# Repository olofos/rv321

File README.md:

# rv321

rv321 is an RISC-V processor implemented using 74HC series logic. Currently the RV32E base instruction set is supported. The design has been simulated using [hneemann's Digital](https://github.com/hneemann/Digital). The simulated circuit also supports the C and Zicsr extensions, though these are not fully implemented in the hardware. The circuit is highly modular, and support for these extra extensions, or for the full RV32I base instruction set, can easily be added by changing only some of the modules.

The rv321 is implemented with a [bit-serial architecture](https://en.wikipedia.org/wiki/Bit-serial_architecture) where, for example, the ALU acts on one bit at a time. This makes the CPU very slow, each instruction requires around 100 clock cycles. The benefit of this architecture is that a one bit ALU is much smaller than a 32-bit ALU and that internal data paths only require a single line instead of a big parallel bus. This makes it possible to implement various modules as individual components connected through simple cables.

## Supported Instructions

The CPU supports all the instructions of the RV32E as well as the C and Zicsr extensions. However, the instructions are not completely decoded, which means that some illegal instructions will be incorrectly interpreted as valid instructions. This mostly affect instruction encodings that are not defined in the RISC-V specification. However, a few encodings that are valid RISC-V instructions, such as `sret` and `uret` will be erroneously decoded instead of raising an illegal instruction exception, even though these instructions are illegal since code on rv321 only runs in machine mode.

## CSRs

Currently the following CSRs are implemented:

* `mstatus`
* `mepc`
* `mtvec`
* `mscratch`
* `mcause`
* `mip`
* `mie`

All other CSRs are read as zero. Note that reading from or writing to an invalid CSR does *not* cause an illegal instruction exception.

## Traps and Interrupts

# Technical Details

The rv321 CPU is microcoded with the code stored in four 128kB parallel flash ROMs. The instructions are decoded by addressing these ROMs by 10 bits of the opcode, together with a six bit step counter and a flag bit, which is used by for example the branch instructions. Each opcode is processed in a number of *steps*, which in turn consist of either one or four *clock cycles*. There are two types of clock cycles: *control cycles* and *bus cycles*. During a control cycle only the control lines are being changed, while bus cycles are used to transfer data along the various internal and external buses. A step with a control cycle is always a single cycle long, but a step with bus cycles can be either one or four cycles long. 

Internal registers are implemented using shift registers that feed back into themselves, effectively creating delay line memories. Because of this, the bus cycles always have to come in groups of 32. Most data transfers are 32 bits and thus automatically take 32 bus cycles to complete anyway. However, there are a couple of cases where a shorter data transfer has to be extended by extra bus cycles to keep the registers in sync. One such examples is storing a single byte to memory, where only 8 cycles are needed for the actual data transfer, but an additional 24 cycles are needed to keep the alignment of the registers (note that a load of an 8 bit byte would always need 32 bus cycles since we need to fill the upper 24 bit with either zeros or the sign extension of the loaded byte). A second example is when transferring a 12 bit CSR address, where a padding of 20 cycles is necessary. These extra dummy bus cycles could have been avoided by gating the bus clock to registers that are not involved in the transfer, but the current design saves a bit of complexity by not introducing extra clock gates and control lines to drive them. 

## The ALU

The ALU supports the following operations:

* Bitwise boolean operations: `and`, `or` and `xor`
* Addition and subtraction
* Comparisons: equality, signed less-than and unsigned less-than
* Logical shift left, logical shift right and arithmetic shift right

The first three sets of operations are fairly straight forward.

The shift operations are more interesting. It does not use a full 32 bit barrel shifter since this would take up quite a bit of space. Instead the HEF4557B variable length shift register is used as intermediate storage during the computation (the same type of shift register is used in several other places in the rv321 as a convenient serial-in serial-out shift register with a fairly large number of bits, but the shifter in the ALU is the only circuitry that takes advantage of the possibility to vary the length of the shift register). The computation of a value shifted left or right by `n` bits goes in several steps:

1. Use the addition circuitry of the ALU to calculate the needed shift register length: `L = 32 + n` for a left shift and `L = 32 - n` for a right shift
1. Configure the HEF4557B shift register to be `L` bits long and clear its content
1. Shift in 32 bits of input data into the shift register
1. Shift out 32 bits of output data from the shift register

If the shift register length `L` is less than 32 (as is the case for a right shift with `n > 0`) we fill the remaining bits with either zero for a logical shift, or with the top bit of the output (the sign bit) for an arithmetic shift. The sign bit is stored in an extra flip flop which is set in the previous step.

As an example let us shift `0x87654321` by 12 bits to the left

1. The length of the shift register is `L = 32 + 12 = 44`.
1. The shift register is cleared. Its content is `0x00000000000`.
1. We shift in our 32 bits of data, starting with the least significant bit. After this the content of the shift register is `0x87654321000`.
1. We shift out 32 bits of output data, starting with the least significant bit. The result is the bottom four bytes of the shift register, `0x54321000`, which is exactly the expected result. The shift register still contains `0x00000000876`, but these bits are never used.

As a second example let us take the arithmetical shift `0x87654321` by 12 bits to the right

1. The length of the shift register is `L = 32 - 12 = 20`.
1. The shift register is cleared. Its content is `0x00000`.
1. We shift in our 32 bits of data, starting with the least significant bit. After this the content of the shift register is `0x87654`. Note that the lowest 12 bits have been discarded since they did not fit in the register.
1. We shift out 32 bits of output data, starting with the least significant bit. Since the shift register now contains less than 32 bits, we repeatedly shift in the sign bit of the input, which is our case is one. The resulting output is `0xFFF87654`, which again is the expected result. The shift register is left containing `0xFFFFF`.

## Possible Optimisations

The bit-serial architecture makes the rv321 CPU very inefficient. However, there is room for optimisation of the current implementation. There are two main steps for each instruction. First the instruction is fetched and then it is executed. The fetching is exactly the same for all instructions. It would be more efficient to begin fetching the next instruction while executing the previous instruction. This would make any instruction that does not affect the program counter or access memory run faster. However, this would require a more complicated reset circuit, to ensure that the very first instruction is properly fetched, and some parts of the circuit are made simpler by the fact that each instruction has a well-defined start and end. Moreover, the program counter is currently always routed through the ALU, so that there is only one source of memory addresses. For the ALU to run simultaneously with the loading of the memory address from the program counter, a new multiplexer would need to be added.

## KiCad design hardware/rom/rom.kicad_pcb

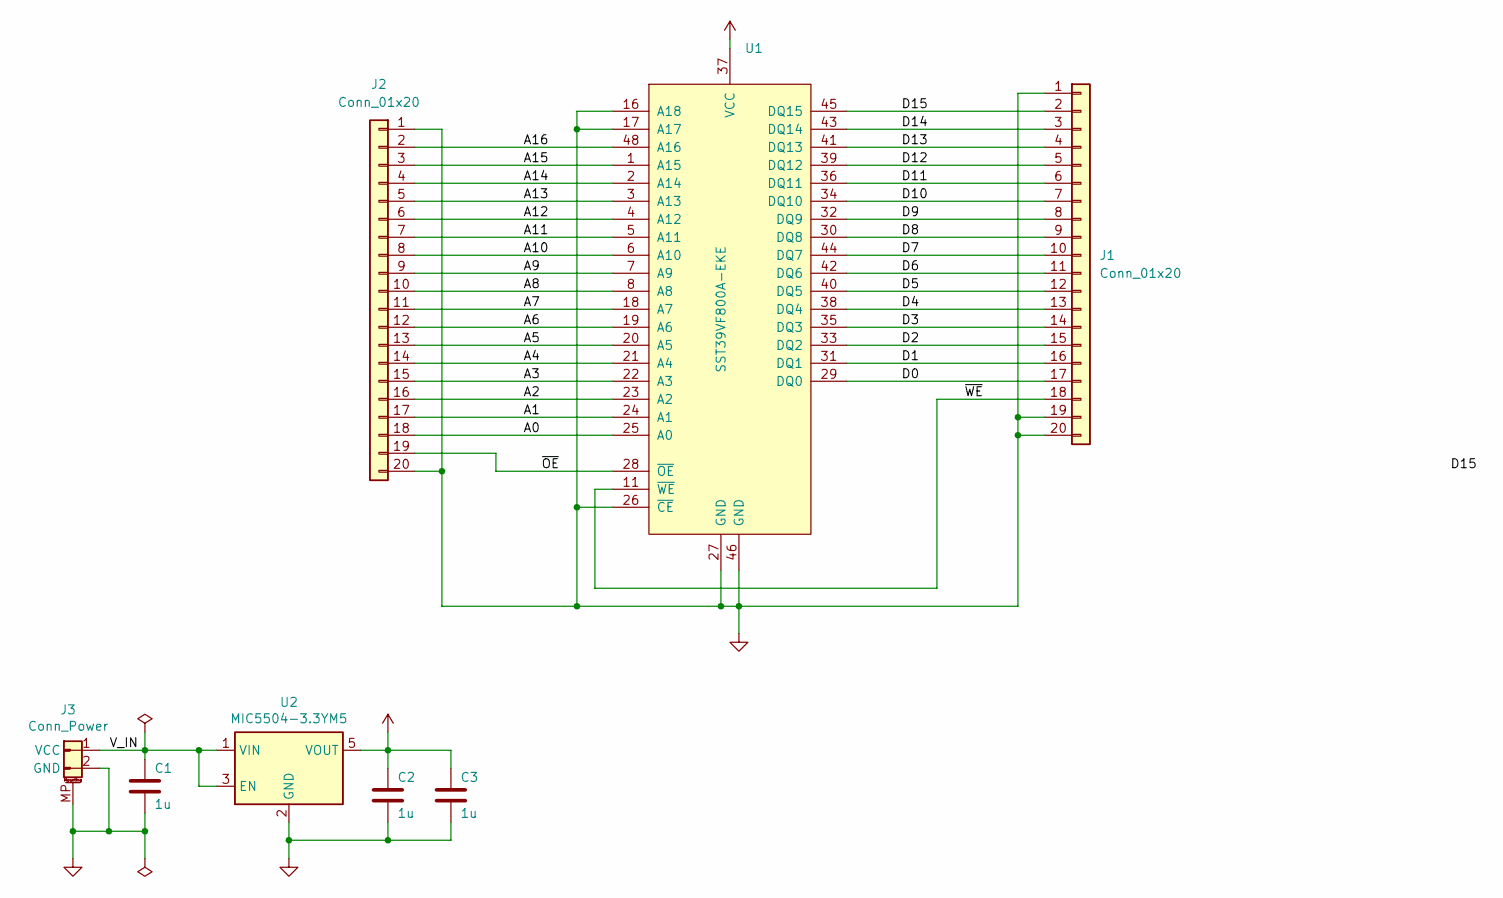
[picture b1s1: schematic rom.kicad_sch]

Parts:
C1, C2, C3: 1u; C_0805_2012Metric_Pad1.18x1.45mm_HandSolder
J1, J2: Conn_01x20; IDC-Header_2x10_P2.54mm_Vertical
J3: Conn_Power; JST_PH_S2B-PH-SM4-TB_1x02-1MP_P2.00mm_Horizontal
U1: SST39VF800A-EKE; TSOP-I-48_18.4x12mm_P0.5mm
U2: MIC5504-3.3YM5; SOT-23-5_HandSoldering

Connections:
/A0: J2.18, U1.25 (A0)
/A1: J2.17, U1.24 (A1)
/A2: J2.16, U1.23 (A2)
/A3: J2.15, U1.22 (A3)
/A4: J2.14, U1.21 (A4)
/A5: J2.13, U1.20 (A5)
/A6: J2.12, U1.19 (A6)
/A7: J2.11, U1.18 (A7)
/A8: J2.10, U1.8 (A8)
/A9: J2.9, U1.7 (A9)
/A10: J2.8, U1.6 (A10)
/A11: J2.7, U1.5 (A11)
/A12: J2.6, U1.4 (A12)
/A13: J2.5, U1.3 (A13)
/A14: J2.4, U1.2 (A14)
/A15: J2.3, U1.1 (A15)
/A16: J2.2, U1.48 (A16)
/D0: J1.17, U1.29 (DQ0)
/D1: J1.16, U1.31 (DQ1)
/D2: J1.15, U1.33 (DQ2)
/D3: J1.14, U1.35 (DQ3)
/D4: J1.13, U1.38 (DQ4)
/D5: J1.12, U1.40 (DQ5)
/D6: J1.11, U1.42 (DQ6)
/D7: J1.10, U1.44 (DQ7)
/D8: J1.9, U1.30 (DQ8)
/D9: J1.8, U1.32 (DQ9)
/D10: J1.7, U1.34 (DQ10)
/D11: J1.6, U1.36 (DQ11)
/D12: J1.5, U1.39 (DQ12)
/D13: J1.4, U1.41 (DQ13)
/D14: J1.3, U1.43 (DQ14)
/D15: J1.2, U1.45 (DQ15)
/V_IN: C1.2, J3.1 (VCC), U2.1 (VIN), U2.3 (EN)
/~OE: J2.19, U1.28 (~OE)
/~WE: J1.18, U1.11 (~WE)
GND: C1.1, C2.1, C3.1, J1.1, J1.19, J1.20, J2.1, J2.20, J3.2 (GND), J3.MP, U1.16 (A18), U1.17 (A17), U1.26 (~CE), U1.27 (GND), U1.46 (GND), U2.2 (GND)
VCC: C2.2, C3.2, U1.37 (VCC), U2.5 (VOUT)

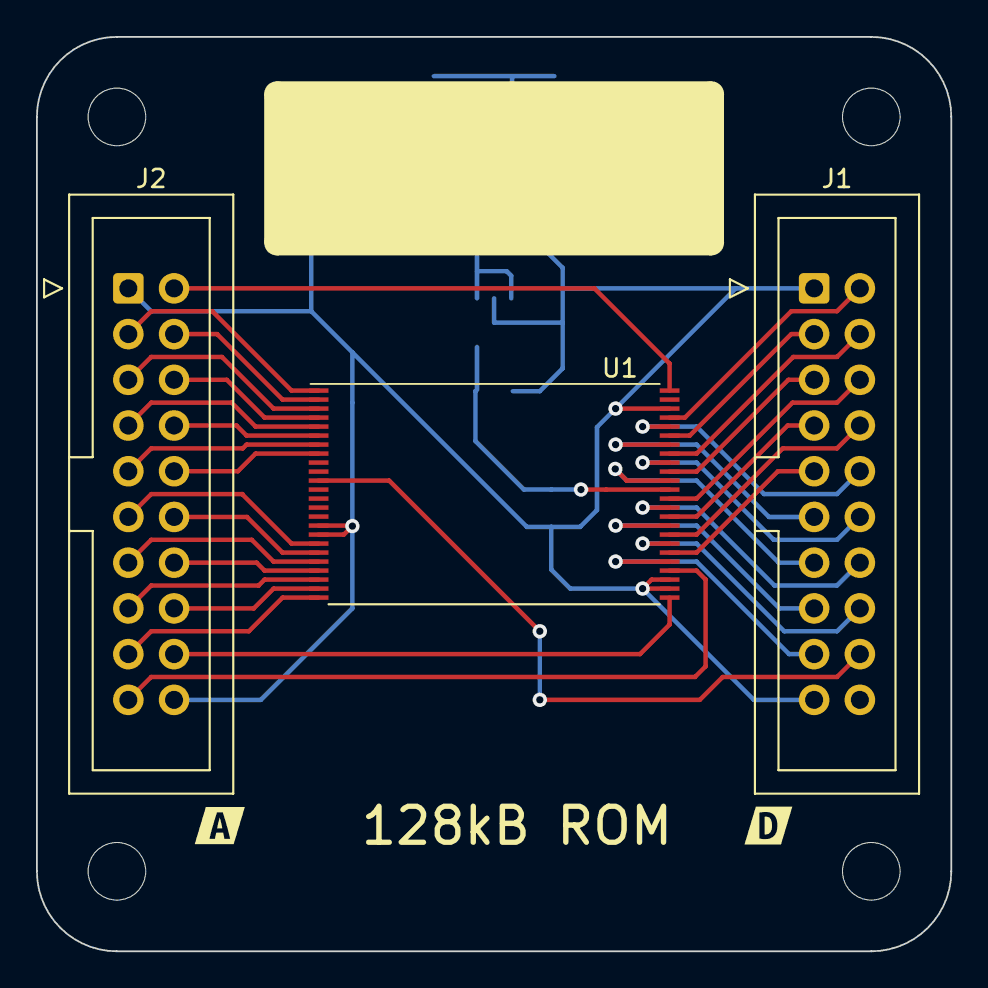
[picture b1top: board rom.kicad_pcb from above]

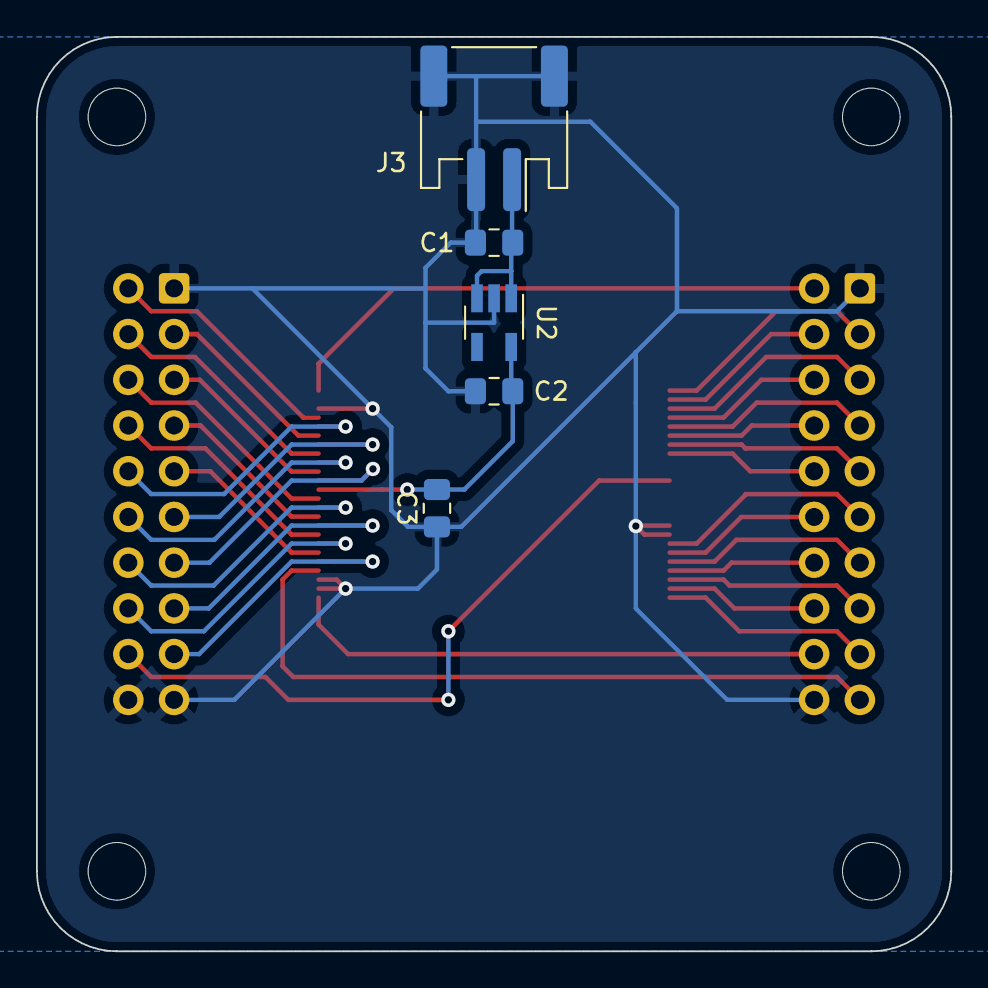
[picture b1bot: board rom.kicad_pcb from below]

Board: 2 copper layers, 50.8 x 50.8 mm, 10 parts (5 on the bottom side), 38 nets.

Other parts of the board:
kibuzzard-635AED85: G***; kibuzzard-635AED85
kibuzzard-635AED97: G***; kibuzzard-635AED97

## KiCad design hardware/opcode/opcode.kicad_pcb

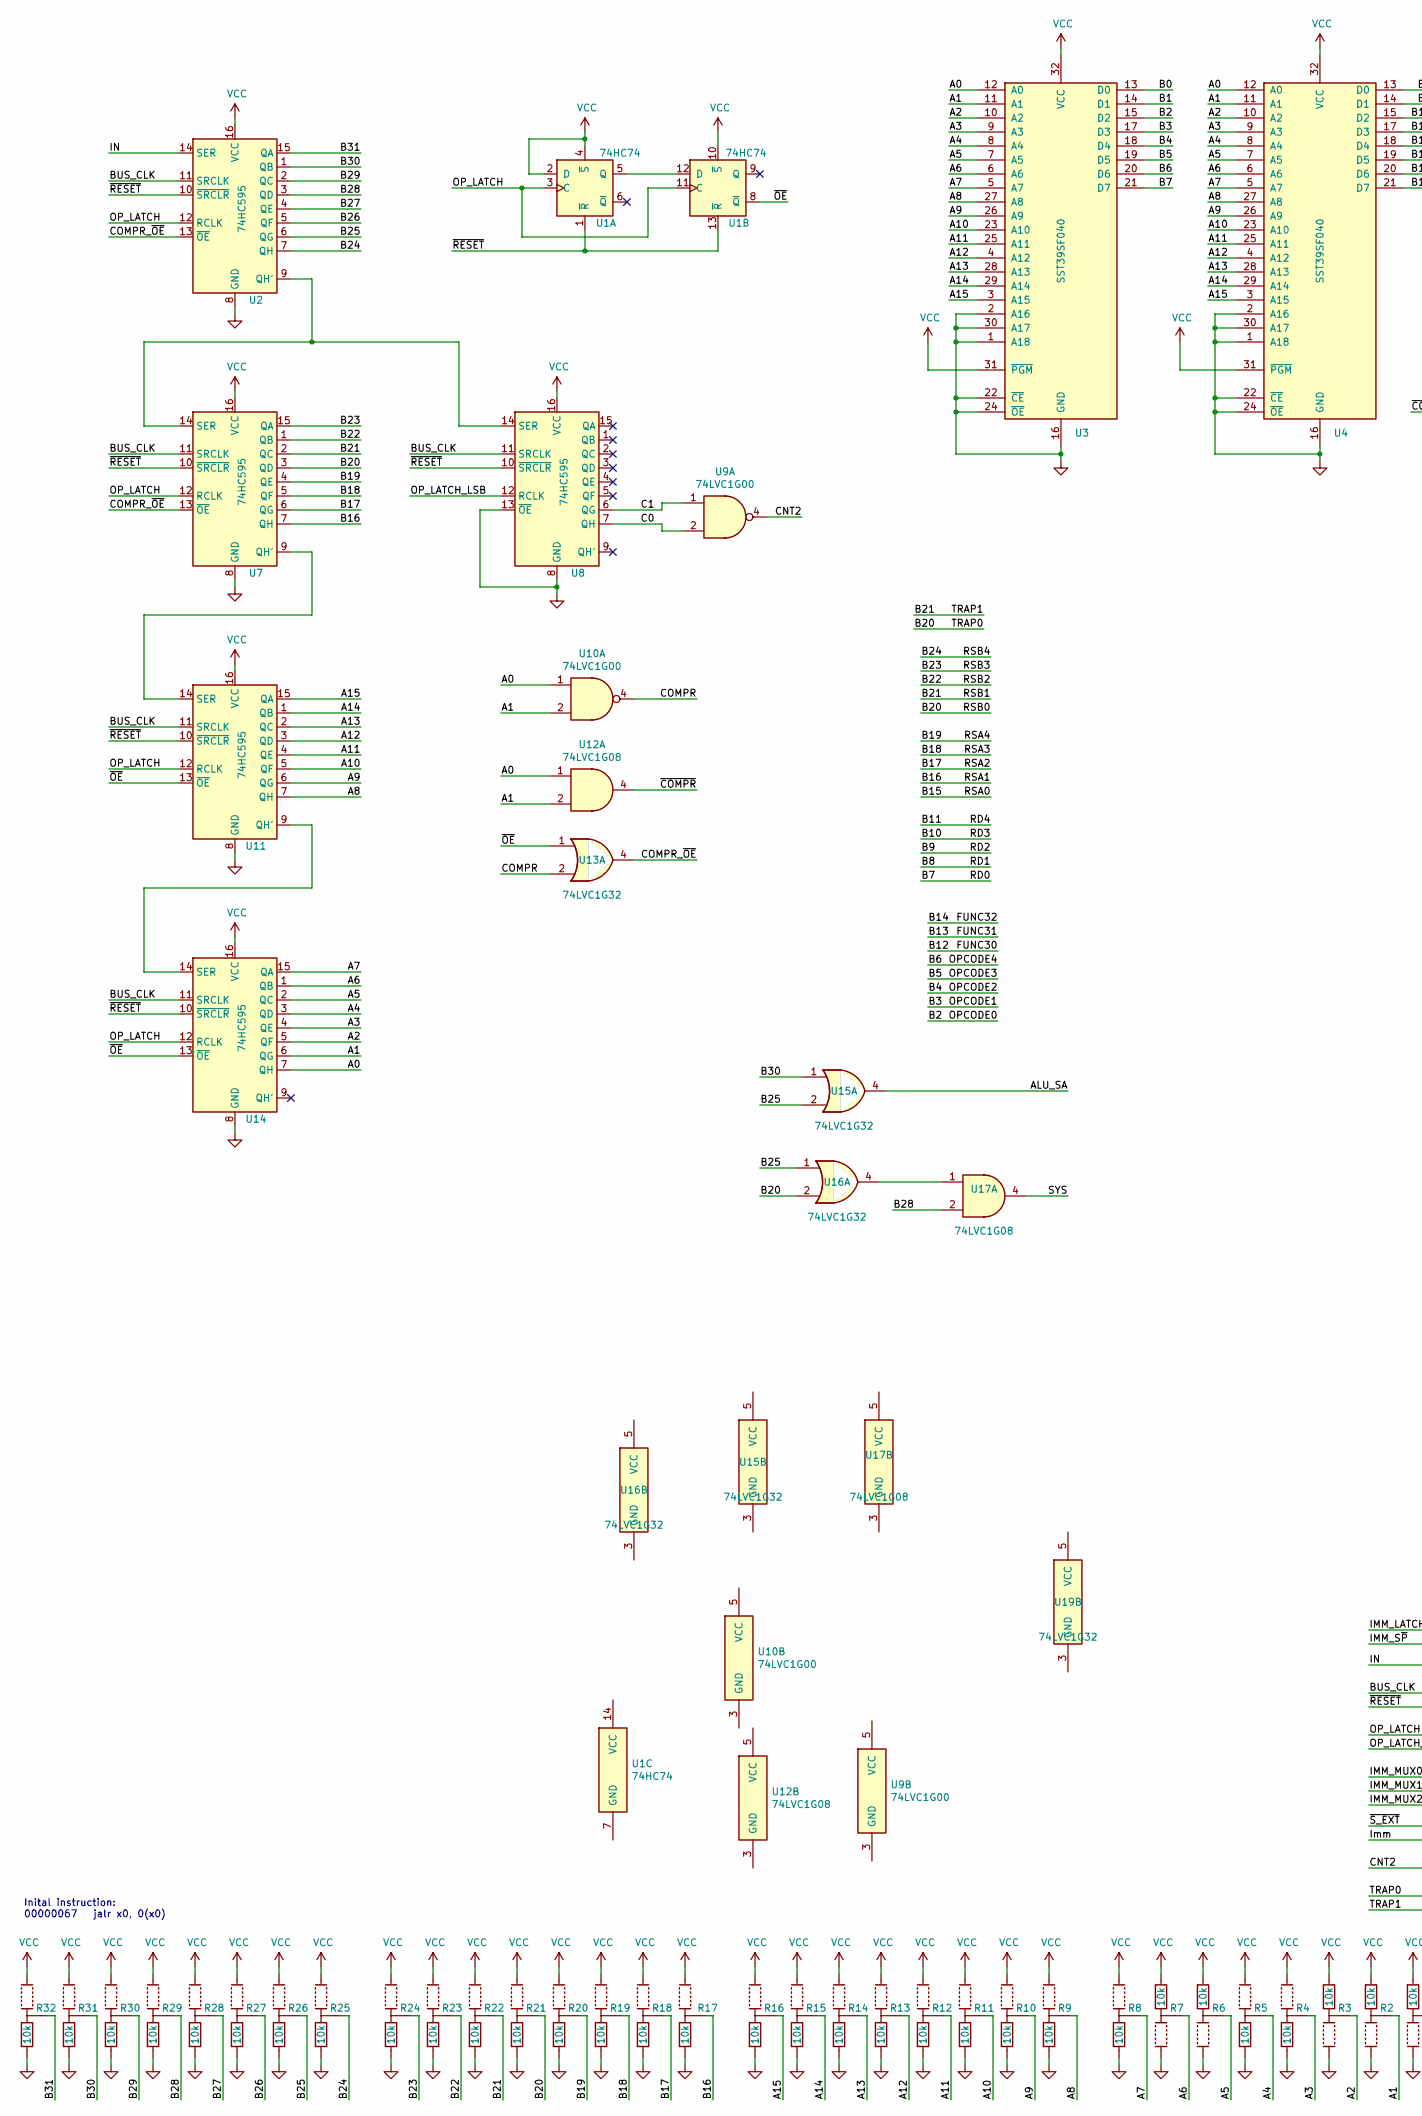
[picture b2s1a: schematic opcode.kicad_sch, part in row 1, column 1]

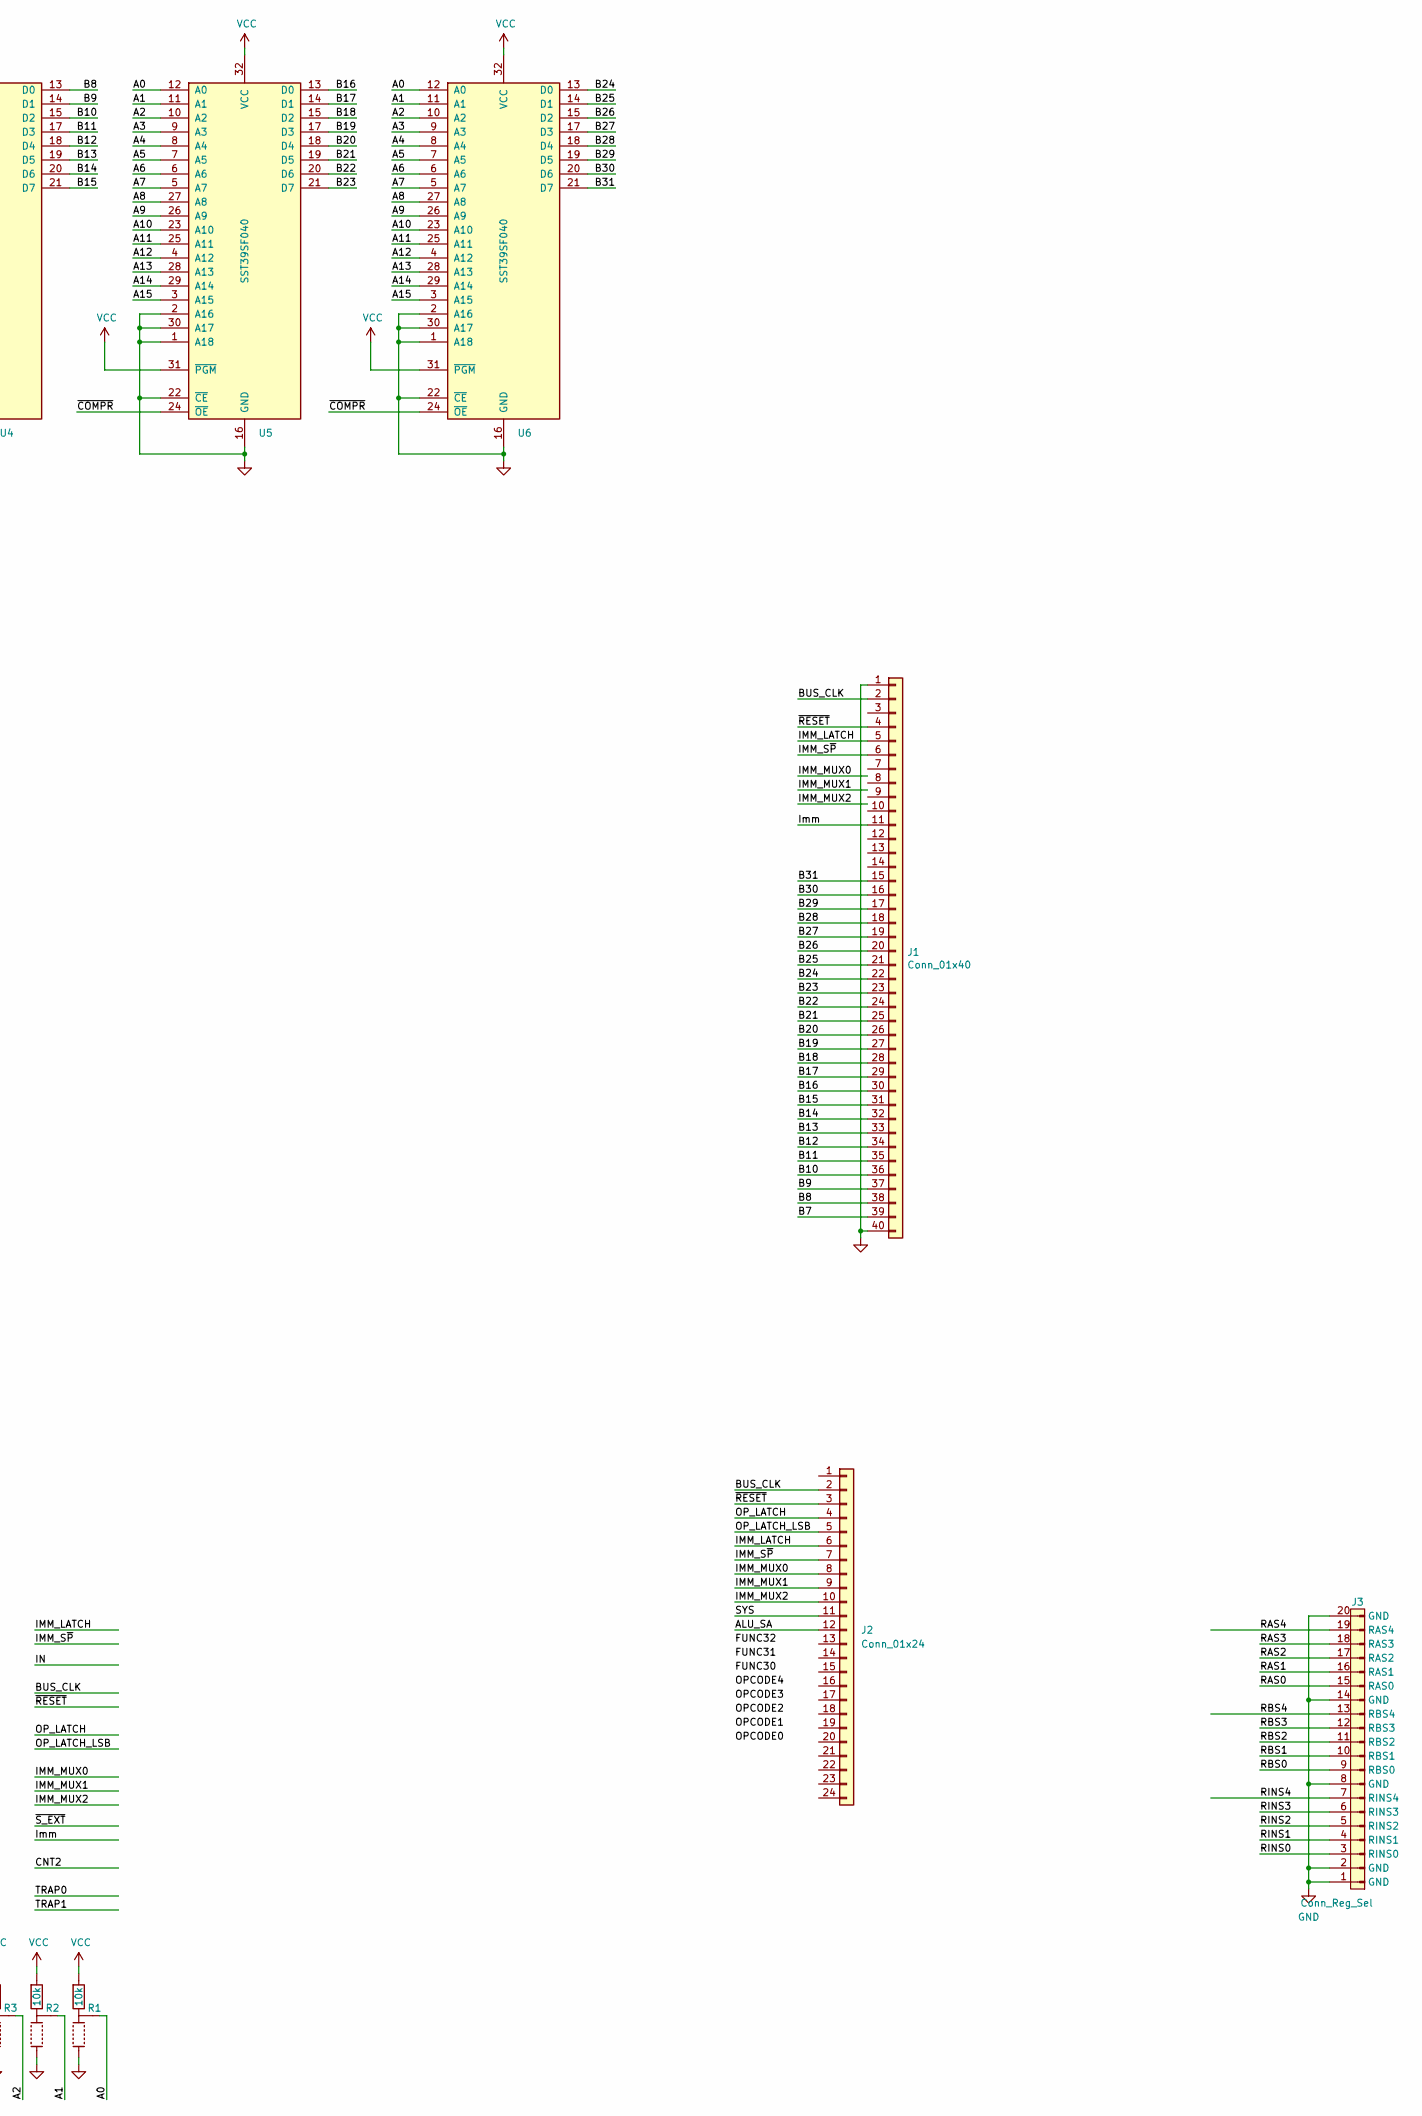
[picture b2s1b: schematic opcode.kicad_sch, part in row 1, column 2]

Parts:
J1: Conn_01x40; IDC-Header_2x20_P2.54mm_Vertical
J2: Conn_01x24; IDC-Header_2x12_P2.54mm_Vertical
J3: Conn_Reg_Sel; IDC-Header_2x10_P2.54mm_Vertical
R1, R2, R3, R4, R5, R6, R7, R8, R9, R10, R11, R12, R13, R14, R15, R16, R17, R18, R19, R20, R21, R22, R23, R24, R25, R26, R27, R28, R29, R30, R31, R32: 10k; Jumper_3_R_0805
U1: 74HC74; SOIC-14_3.9x8.7mm_P1.27mm
U2, U7, U8, U11, U14: 74HC595; SOIC-16_3.9x9.9mm_P1.27mm
U3, U4, U5, U6: SST39SF040; PLCC-32-socket-2M-8432-11B1-RK-TP
U9, U10: 74LVC1G00; SOT-23-5_HandSoldering
U12, U17: 74LVC1G08; SOT-23-5_HandSoldering
U13, U15, U16, U19: 74LVC1G32; SOT-23-5_HandSoldering

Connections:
/A0: R1.2, U3.12 (A0), U4.12 (A0), U5.12 (A0), U6.12 (A0), U10.1, U12.1, U14.7 (QH)
/A1: R2.2, U3.11 (A1), U4.11 (A1), U5.11 (A1), U6.11 (A1), U10.2, U12.2, U14.6 (QG)
/A2: R3.2, U3.10 (A2), U4.10 (A2), U5.10 (A2), U6.10 (A2), U14.5 (QF)
/A3: R4.2, U3.9 (A3), U4.9 (A3), U5.9 (A3), U6.9 (A3), U14.4 (QE)
/A4: R5.2, U3.8 (A4), U4.8 (A4), U5.8 (A4), U6.8 (A4), U14.3 (QD)
/A5: R6.2, U3.7 (A5), U4.7 (A5), U5.7 (A5), U6.7 (A5), U14.2 (QC)
/A6: R7.2, U3.6 (A6), U4.6 (A6), U5.6 (A6), U6.6 (A6), U14.1 (QB)
/A7: R8.2, U3.5 (A7), U4.5 (A7), U5.5 (A7), U6.5 (A7), U14.15 (QA)
/A8: R9.2, U3.27 (A8), U4.27 (A8), U5.27 (A8), U6.27 (A8), U11.7 (QH)
/A9: R10.2, U3.26 (A9), U4.26 (A9), U5.26 (A9), U6.26 (A9), U11.6 (QG)
/A10: R11.2, U3.23 (A10), U4.23 (A10), U5.23 (A10), U6.23 (A10), U11.5 (QF)
/A11: R12.2, U3.25 (A11), U4.25 (A11), U5.25 (A11), U6.25 (A11), U11.4 (QE)
/A12: R13.2, U3.4 (A12), U4.4 (A12), U5.4 (A12), U6.4 (A12), U11.3 (QD)
/A13: R14.2, U3.28 (A13), U4.28 (A13), U5.28 (A13), U6.28 (A13), U11.2 (QC)
/A14: R15.2, U3.29 (A14), U4.29 (A14), U5.29 (A14), U6.29 (A14), U11.1 (QB)
/A15: R16.2, U3.3 (A15), U4.3 (A15), U5.3 (A15), U6.3 (A15), U11.15 (QA)
/ALU_SA: J2.12, U15.4
/B0: U3.13 (D0)
/B1: U3.14 (D1)
/B2: U3.15 (D2)
/B3: U3.17 (D3)
/B4: U3.18 (D4)
/B5: U3.19 (D5)
/B6: U3.20 (D6)
/B7: J1.39, U3.21 (D7)
/B8: J1.38, U4.13 (D0)
/B9: J1.37, U4.14 (D1)
/B10: J1.36, U4.15 (D2)
/B11: J1.35, U4.17 (D3)
/B12: J1.34, U4.18 (D4)
/B13: J1.33, U4.19 (D5)
/B14: J1.32, U4.20 (D6)
/B15: J1.31, U4.21 (D7)
/B16: J1.30, R17.2, U5.13 (D0), U7.7 (QH)
/B17: J1.29, R18.2, U5.14 (D1), U7.6 (QG)
/B18: J1.28, R19.2, U5.15 (D2), U7.5 (QF)
/B19: J1.27, R20.2, U5.17 (D3), U7.4 (QE)
/B20: J1.26, R21.2, U5.18 (D4), U7.3 (QD), U16.2
/B21: J1.25, R22.2, U5.19 (D5), U7.2 (QC)
/B22: J1.24, R23.2, U5.20 (D6), U7.1 (QB)
/B23: J1.23, R24.2, U5.21 (D7), U7.15 (QA)
/B24: J1.22, R25.2, U2.7 (QH), U6.13 (D0)
/B25: J1.21, R26.2, U2.6 (QG), U6.14 (D1), U15.2, U16.1
/B26: J1.20, R27.2, U2.5 (QF), U6.15 (D2)
/B27: J1.19, R28.2, U2.4 (QE), U6.17 (D3)
/B28: J1.18, R29.2, U2.3 (QD), U6.18 (D4), U17.2
/B29: J1.17, R30.2, U2.2 (QC), U6.19 (D5)
/B30: J1.16, R31.2, U2.1 (QB), U6.20 (D6), U15.1
/B31: J1.15, R32.2, U2.15 (QA), U6.21 (D7)
/BUS_CLK: J1.2, J2.2, U2.11 (SRCLK), U7.11 (SRCLK), U8.11 (SRCLK), U11.11 (SRCLK), U14.11 (SRCLK)
/C0: U8.7 (QH), U9.2
/C1: U8.6 (QG), U9.1
/CNT2: U9.4
/COMPR: U10.4, U13.2
/COMPR_~OE: U2.13 (~OE), U7.13 (~OE), U13.4
/IMM_LATCH: J1.5, J2.6
/IMM_MUX0: J2.8
/IMM_MUX1: J2.9
/IMM_MUX2: J2.10
/IMM_S~P: J1.6, J2.7
/IN: U2.14 (SER)
/Imm: J1.11
/OP_LATCH: J2.4, U1.3 (C), U1.11 (C), U2.12 (RCLK), U7.12 (RCLK), U11.12 (RCLK), U14.12 (RCLK)
/OP_LATCH_LSB: J2.5, U8.12 (RCLK)
/RAS0: J3.15 (RAS0)
/RAS1: J3.16 (RAS1)
/RAS2: J3.17 (RAS2)
/RAS3: J3.18 (RAS3)
/RAS4: J3.19 (RAS4)
/RBS0: J3.9 (RBS0)
/RBS1: J3.10 (RBS1)
/RBS2: J3.11 (RBS2)
/RBS3: J3.12 (RBS3)
/RBS4: J3.13 (RBS4)
/RINS0: J3.3 (RINS0)
/RINS1: J3.4 (RINS1)
/RINS2: J3.5 (RINS2)
/RINS3: J3.6 (RINS3)
/RINS4: J3.7 (RINS4)
/SYS: J2.11, U17.4
/~COMPR: U5.24 (~OE), U6.24 (~OE), U12.4
/~OE: U1.8 (~Q), U11.13 (~OE), U13.1, U14.13 (~OE)
/~RESET: J1.4, J2.3, U1.1 (~R), U1.13 (~R), U2.10 (~SRCLR), U7.10 (~SRCLR), U8.10 (~SRCLR), U11.10 (~SRCLR), U14.10 (~SRCLR)
GND: J1.1, J1.40, J3.1 (GND), J3.2 (GND), J3.8 (GND), J3.14 (GND), J3.20 (GND), R1.3, R2.3, R3.3, R4.1, R5.1, R6.3, R7.3, R8.1, R9.1, R10.1, R11.1, R12.1, R13.1, R14.1, R15.1, R16.1, R17.1, R18.1, R19.1, R20.1, R21.1, R22.1, R23.1, R24.1, R25.1, R26.1, R27.1, R28.1, R29.1, R30.1, R31.1, R32.1, U2.8 (GND), U3.1 (A18), U3.2 (A16), U3.16 (GND), U3.22 (~CE), U3.24 (~OE), U3.30 (A17), U4.1 (A18), U4.2 (A16), U4.16 (GND), U4.22 (~CE), U4.24 (~OE), U4.30 (A17), U5.1 (A18), U5.2 (A16), U5.16 (GND), U5.22 (~CE), U5.30 (A17), U6.1 (A18), U6.2 (A16), U6.16 (GND), U6.22 (~CE), U6.30 (A17), U7.8 (GND), U8.8 (GND), U8.13 (~OE), U11.8 (GND), U14.8 (GND)
unnamed: U1.5 (Q), U1.12 (D)
unnamed: U2.9 (QH'), U7.14 (SER), U8.14 (SER)
unnamed: U11.9 (QH'), U14.14 (SER)
unnamed: U7.9 (QH'), U11.14 (SER)
unnamed: U16.4, U17.1
VCC: R1.1, R2.1, R3.1, R4.3, R5.3, R6.1, R7.1, R8.3, R9.3, R10.3, R11.3, R12.3, R13.3, R14.3, R15.3, R16.3, R17.3, R18.3, R19.3, R20.3, R21.3, R22.3, R23.3, R24.3, R25.3, R26.3, R27.3, R28.3, R29.3, R30.3, R31.3, R32.3, U1.2 (D), U1.4 (~S), U1.10 (~S), U2.16 (VCC), U3.31 (~PGM), U3.32 (VCC), U4.31 (~PGM), U4.32 (VCC), U5.31 (~PGM), U5.32 (VCC), U6.31 (~PGM), U6.32 (VCC), U7.16 (VCC), U8.16 (VCC), U11.16 (VCC), U14.16 (VCC)

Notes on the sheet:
Inital instruction: 00000067 jalr x0, 0(x0)

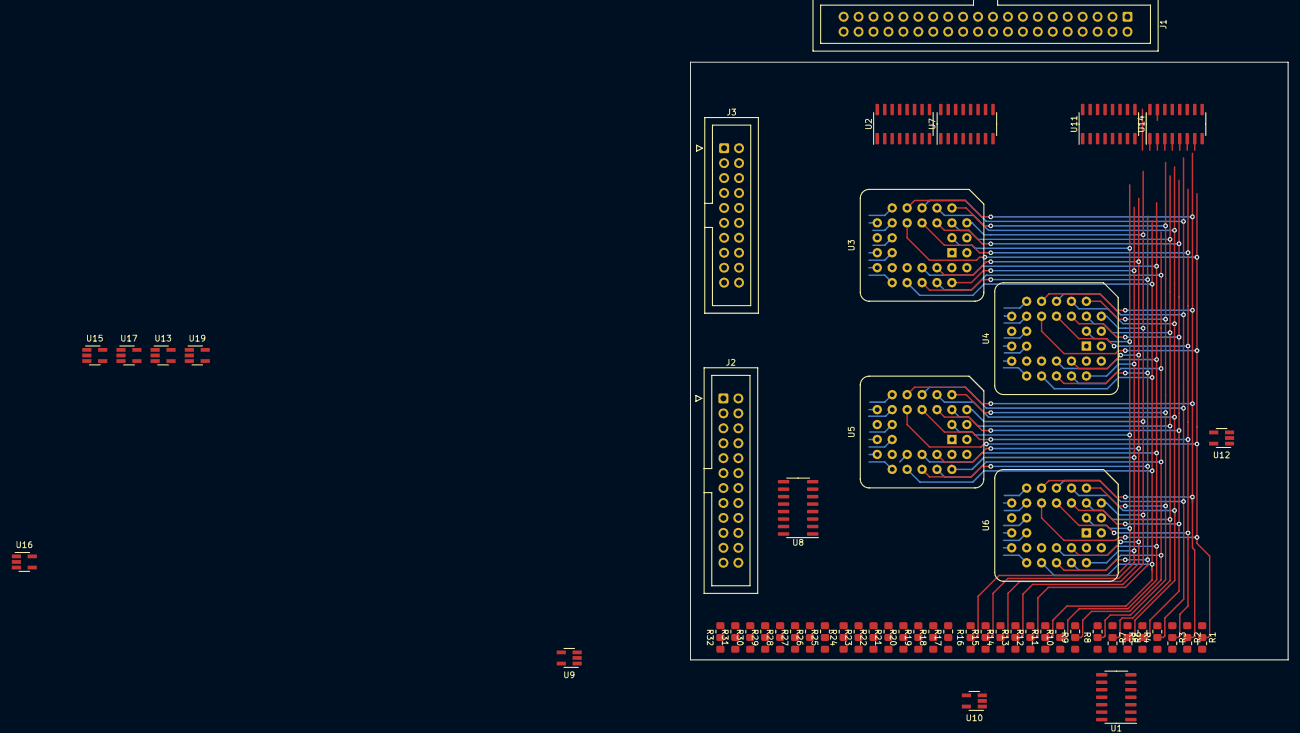
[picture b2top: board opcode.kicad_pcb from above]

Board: 4 copper layers, 101.6 x 101.6 mm, 53 parts (0 on the bottom side), 62 nets.
